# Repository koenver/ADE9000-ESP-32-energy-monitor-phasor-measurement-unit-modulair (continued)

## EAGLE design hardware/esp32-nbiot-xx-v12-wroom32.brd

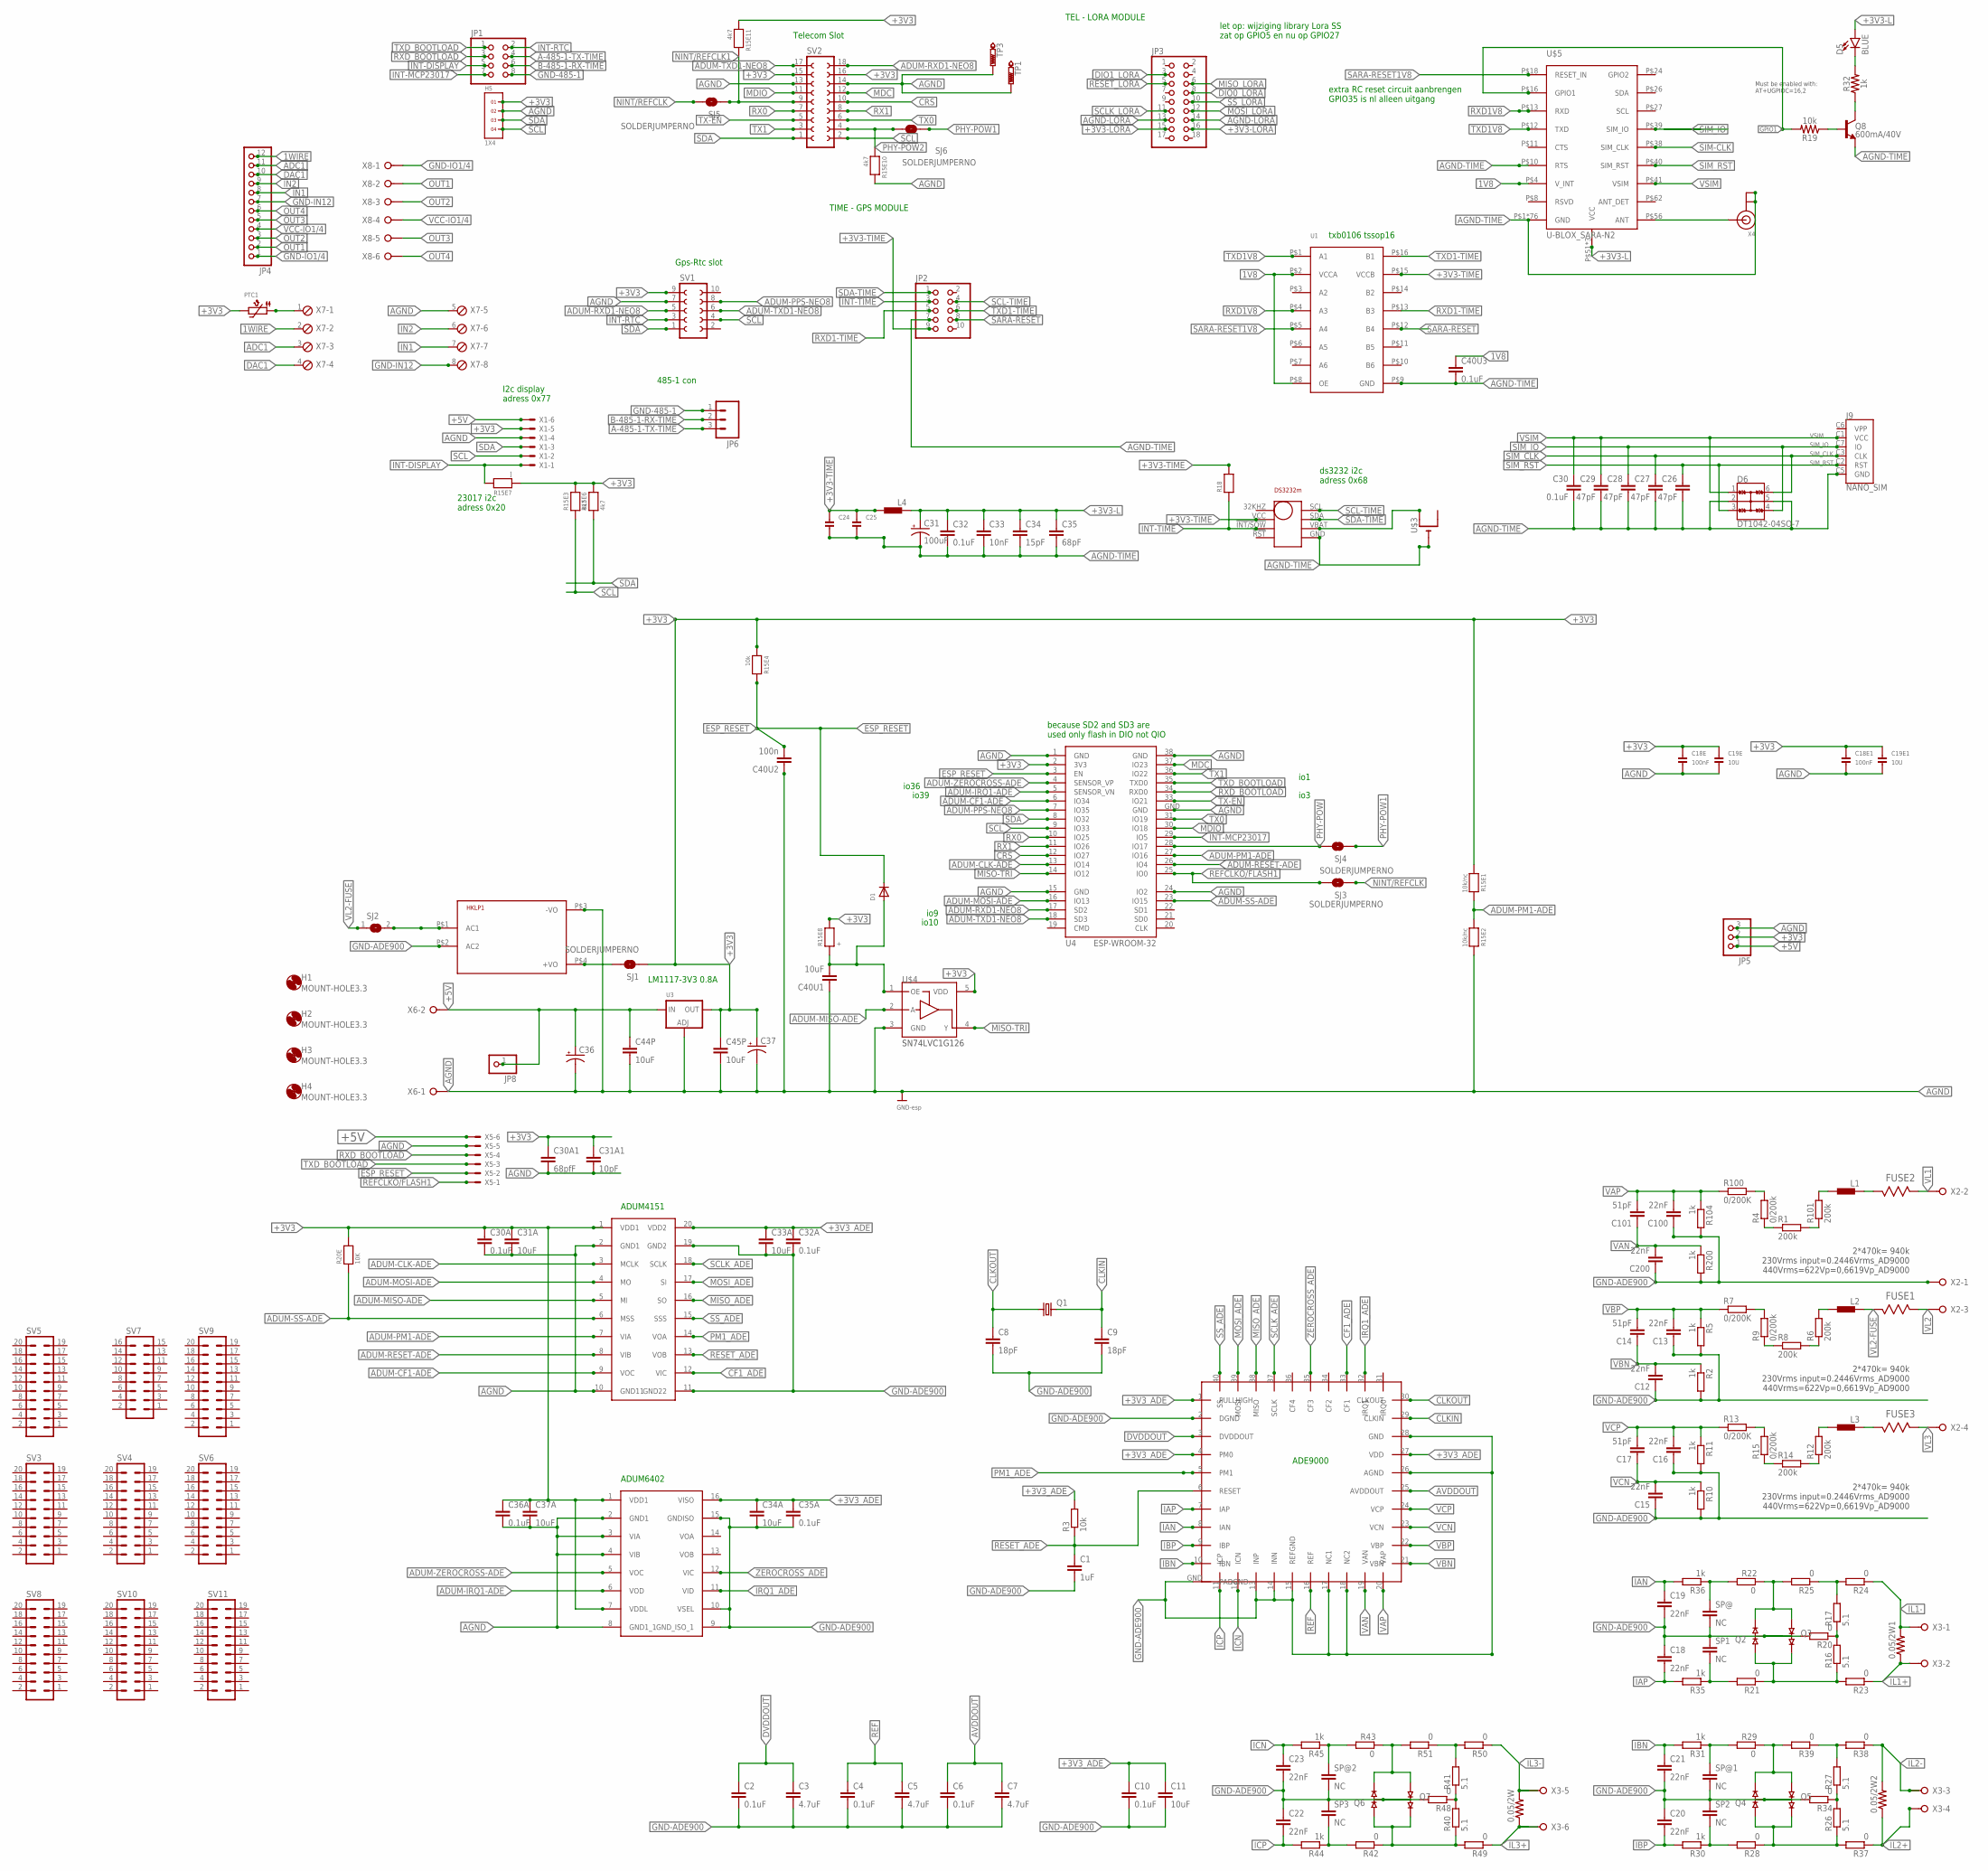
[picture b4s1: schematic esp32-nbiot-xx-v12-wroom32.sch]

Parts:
0.05/2W, 0.05/2W1, 0.05/2W2: R-US_R4527; R4527
ADE9000: ADE9000; LFCSP40
ADUM4151: ADUM4151; SOIC20R
ADUM6402-2: ADUM6402; SOIC16R
C1: 1uF; C0805
C2, C4, C6, C10, C30A, C32A, C35A, C36A, C40U3: 0.1uF; C0805
C3, C5, C7: 4.7uF; C0805
C8, C9: 18pF; C0805
C11, C31A, C33A, C34A, C37A, C40U1, C44P, C45P: 10uF; C0805
C12, C13, C15, C16, C18, C19, C20, C21, C22, C23, C100, C200: 22nF; C0805
C14, C17, C101: 51pF; C0805
C18E, C18E1: 100nF; _0805
C19E, C19E1: 10U; _0805
C24, C25: CAP_CERAMIC0805; 0805
C26, C27, C28, C29: 47pF; 0603
C30, C32: 0.1uF; 0603
C30A1: 68pfF; C0805
C31: 100uF; 1206-POLAR
C31A1: 10pF; C0805
C33: 10nF; 0603
C34: 15pF; 0603
C35: 68pF; 0603
C36, C37: CPOL-USD/7343-31R; D/7343-31R
C40U2: 100n; C0805
D1: DIODE_SOD-123FL; SOD-123FL
D5: BLUE; LED-0603
D6: DT1042-04SO-7; SOT23-6L
FUSE1, FUSE2, FUSE3: CRCW25124R70JNEG; RESC6332X71N
H1, H2, H3, H4: MOUNT-HOLE3.3; 3,3
H5: 1X4
HKLP1: HKLPM01
J9: NANO_SIM; NANO_SIM_WURTH_693043020611
JP1: PINHD-2X4; 2X04
JP2: PINHD-2X5/90; 2X05/90
JP3: PINHD-2X9/90; 2X09/90
JP4: PINHD-1X12; 1X12
JP5: PINHD-1X3; 1X03
JP6: M03SCREW; SCREWTERMINAL-3.5MM-3
JP8: PINHD-1X1; 1X01
L1, L2, L3, L4: 1500; M0805; DIGIKEY 490-1048-1-ND
PTC1: PTC1206; 1206
Q1: CRYSTALCTS406; CTS406
Q2, Q3, Q4, Q5, Q6, Q7: MMBD4148SE; SOT23-3; DIGIKEY MMBD4148SECT-ND
Q8: 600mA/40V; SOT23-3
R1, R6, R8, R12, R14, R101: 200k; M1206
R2, R5, R10, R11, R104, R200: 1k; M0805
R3: 10k; M0805
R4, R9, R15: 0/200k; M1206
R7, R13, R100: 0/200K; M1206
R15E1, R15E2: 10k/nc; _0805
R15E3, R15E6, R15E10, R15E11: 4k7; _0805
R15E4: 10k; _0805
R15E7: ]; _0805
R15E8: +; _0805
R16, R26, R40: 5.1; R0805; MFR_PART_NO_# CPF0805B5R1E1
R17, R27, R41: 5.1; R0805
R18: RESISTOR0805; 0805
R19: 10k; 0603
R20, R21, R22, R23, R24, R25, R28, R29, R34, R37, R38, R39, R42, R43, R48, R49, R50, R51: 0; R0603
R20E: 10K; _0805
R30, R31, R35, R36, R44, R45: 1k; R0603
R32: 1k; 0603
SJ1, SJ3, SJ4, SJ5, SJ6: SOLDERJUMPERNO; SJ_2S-NO
SJ2: SOLDERJUMPERWAVE; SOLDERJUMPER_WAVE
SP1, SP2, SP3: NC; C0805
SP@, SP@1, SP@2: NC; C0805
SV1: FE05-2W
SV2: FE09-2W
SV3, SV4, SV5, SV6, SV8, SV9, SV10, SV11: MA10-2
SV7: MA08-2
TP1, TP3: PTR1TP08SQ; TP08SQ
U1: TXB0106; TSSOP16
U3: LM1117SOT223-REFLOW; SOT223-R
U4: ESP-WROOM-32
U$1: DS3232M; SOIC8
U$3: CR1220SMT; CR1220-SMD
U$4: SN74LVC1G126DBVT; SOT-23-5L
U$5: U-BLOX_SARA-N2; SARA-N2
X1, X5: 22-23-2061
X2: W237-04P; W237-4P
X3, X8: W237-06P; W237-6P
X4: ANTENNA_U.FL; U.FL
X6: W237-02P; W237-132
X7: MPT8; 8POL254

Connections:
1V8: C40U3.1, U1.P$2 (VCCA), U1.P$8 (OE), U$5.P$4 (V_INT)
1WIRE: JP4.12, X7.2
+3V3: ADUM4151.1 (VDD1), ADUM6402-2.1 (VDD1), ADUM6402-2.7 (VDDL), C18E.1, C18E1.1, C19E.1, C19E1.1, C30A.1, C30A1.1, C31A.1, C31A1.1, C36A.1, C37.+, C37A.1, C45P.1, H5.1, JP5.2, PTC1.2, R15E1.1, R15E3.2, R15E4.1, R15E6.2, R15E7.1, R15E8.2, R15E11.1, R20E.2, SJ1.1, SV1.9, SV2.15, SV2.16, U3.2 (OUT), U4.2 (3V3), U$4.5 (VDD), X1.5
+3V3-L: C31.1 (+), C32.1, C33.1, C34.1, C35.1, D5.A, L4.1, U$5.P$51 (VCC), U$5.P$52 (VCC), U$5.P$53 (VCC)
+3V3-LORA: JP3.15, JP3.16
+3V3-TIME: C24.1, C25.1, JP2.9, L4.2, R18.2, U1.P$15 (VCCB), U$1.VCC
+3V3FUSE: PTC1.1, X7.1
+3V3_ADE: ADE9000.1 (PULLHIGH), ADE9000.4 (PM0), ADE9000.27 (VDD), ADUM4151.20 (VDD2), ADUM6402-2.16 (VISO), C10.1, C11.1, C32A.1, C33A.1, C34A.1, C35A.1, R3.2
+5V: C36.+, C44P.1, JP5.1, JP8.1, U3.3 (IN), X1.6, X5.6, X6.2
A-485-1-TX-TIME: JP1.4, JP6.3
ADC1: JP4.11, X7.3
ADUM-CF1-ADE: ADUM4151.9 (VOC), U4.6 (IO34)
ADUM-CLK-ADE: ADUM4151.3 (MCLK), U4.13 (IO14)
ADUM-IRQ1-ADE: ADUM6402-2.6 (VOD), U4.5 (SENSOR_VN)
ADUM-MISO-ADE: ADUM4151.5 (MI), U$4.2 (A)
ADUM-MOSI-ADE: ADUM4151.4 (MO), U4.16 (IO13)
ADUM-PM1-ADE: ADUM4151.7 (VIA), R15E1.2, R15E2.1, U4.27 (IO16)
ADUM-PPS-NEO8: SV1.8, U4.7 (IO35)
ADUM-RESET-ADE: ADUM4151.8 (VIB), U4.26 (IO4)
ADUM-RXD1-NEO8: SV1.5, SV2.18, U4.17 (SD2)
ADUM-SS-ADE: ADUM4151.6 (MSS), R20E.1, U4.23 (IO15)
ADUM-TXD1-NEO8: SV1.6, SV2.17, U4.18 (SD3)
ADUM-ZEROCROSS-ADE: ADUM6402-2.5 (VOC), U4.4 (SENSOR_VP)
AGND: ADUM4151.2 (GND1), ADUM4151.10 (GND11), ADUM6402-2.2 (GND1), ADUM6402-2.3 (VIA), ADUM6402-2.4 (VIB), ADUM6402-2.8 (GND1_1), C18E.2, C18E1.2, C19E.2, C19E1.2, C30A.2, C30A1.2, C31A.2, C31A1.2, C36.-, C36A.2, C37.-, C37A.2, C40U1.1, C40U2.1, C44P.2, C45P.2, H5.2, HKLP1.P$3 (-VO), JP5.3, R15E2.2, R15E10.2, SV1.7, SV2.13, SV2.14, TP1.TP, TP3.TP, U3.1 (ADJ), U4.1 (GND), U4.15 (GND), U4.24 (IO2), U4.38 (GND), U4.GND, U$4.3 (GND), X1.4, X5.5, X6.1, X7.5
AGND-LORA: JP3.13, JP3.14
AGND-TIME: C24.2, C25.2, C26.2, C27.2, C28.2, C29.2, C30.2, C31.2 (-), C32.2, C33.2, C34.2, C35.2, C40U3.2, D6.2, D6.5, J9.C5 (GND), JP2.7, Q8.2 (E), U1.P$9 (GND), U$1.GND, U$3.-, U$5.P$1 (GND), U$5.P$2 (GND), U$5.P$3 (GND), U$5.P$5 (GND), U$5.P$6 (GND), U$5.P$7 (GND), U$5.P$9 (GND), U$5.P$10 (RTS), U$5.P$14 (GND), U$5.P$15 (GND), U$5.P$17 (GND), U$5.P$19 (GND), U$5.P$20 (GND), U$5.P$21 (GND), U$5.P$22 (GND), U$5.P$23 (GND), U$5.P$25 (GND), U$5.P$28 (GND), U$5.P$29 (GND), U$5.P$30 (GND), U$5.P$31 (GND), U$5.P$32 (GND), U$5.P$33 (GND), U$5.P$34 (GND), U$5.P$35 (GND), U$5.P$36 (GND), U$5.P$37 (GND), U$5.P$42 (GND), U$5.P$43 (GND), U$5.P$44 (GND), U$5.P$45 (GND), U$5.P$46 (GND), U$5.P$47 (GND), U$5.P$48 (GND), U$5.P$49 (GND), U$5.P$50 (GND), U$5.P$54 (GND), U$5.P$55 (GND), U$5.P$57 (GND), U$5.P$58 (GND), U$5.P$59 (GND), U$5.P$60 (GND), U$5.P$61 (GND), U$5.P$63 (GND), U$5.P$64 (GND), U$5.P$65 (GND), U$5.P$66 (GND), U$5.P$67 (GND), U$5.P$68 (GND), U$5.P$69 (GND), U$5.P$70 (GND), U$5.P$71 (GND), U$5.P$72 (GND), U$5.P$73 (GND), U$5.P$74 (GND), U$5.P$75 (GND), U$5.P$76 (GND), U$5.P$77 (GND), U$5.P$78 (GND), U$5.P$79 (GND), U$5.P$80 (GND), U$5.P$81 (GND), U$5.P$82 (GND), U$5.P$83 (GND), U$5.P$84 (GND), U$5.P$85 (GND), U$5.P$86 (GND), U$5.P$87 (GND), U$5.P$88 (GND), U$5.P$89 (GND), U$5.P$90 (GND), U$5.P$91 (GND), U$5.P$92 (GND), U$5.P$93 (GND), U$5.P$94 (GND), U$5.P$95 (GND), U$5.P$96 (GND), X4.1 (GND), X4.2 (GND)
AVDDOUT: ADE9000.25 (AVDDOUT), C6.1, C7.1
B-485-1-RX-TIME: JP1.6, JP6.2
CF1_ADE: ADE9000.33 (CF1), ADUM4151.12 (VIC)
CLKIN: ADE9000.29 (CLKIN), C9.1, Q1.3 (2)
CLKOUT: ADE9000.30 (CLKOUT), C8.1, Q1.1
CRS: SV2.10, U4.12 (IO27)
DAC1: JP4.10, X7.4
DIO0_LORA: JP3.8
DIO1_LORA: JP3.3
DVDDOUT: ADE9000.3 (DVDDOUT), C2.1, C3.1
ESP_RESET: C40U2.2, D1.C, R15E4.2, U4.3 (EN), X5.2
GND-485-1: JP1.8, JP6.1
GND-ADE900: ADE9000.2 (DGND), ADE9000.13 (INP), ADE9000.14 (INN), ADE9000.15 (REFGND), ADE9000.17 (NC1), ADE9000.18 (NC2), ADE9000.26 (AGND), ADE9000.28 (GND), ADE9000.GND, ADUM4151.11 (GND22), ADUM4151.19 (GND2), ADUM6402-2.9 (GND_ISO_1), ADUM6402-2.10 (VSEL), ADUM6402-2.15 (GNDISO), C1.2, C2.2, C3.2, C4.2, C5.2, C6.2, C7.2, C8.2, C9.2, C10.2, C11.2, C12.1, C13.1, C15.1, C16.1, C18.1, C19.2, C20.1, C21.2, C22.1, C23.2, C32A.2, C33A.2, C34A.2, C35A.2, C100.1, C200.1, HKLP1.P$2 (AC2), Q2.3, Q3.3, Q4.3, Q5.3, Q6.3, Q7.3, R2.2, R5.2, R10.2, R11.2, R20.2, R34.2, R48.2, R104.2, R200.2, SP1.1, SP2.1, SP3.1, SP@.2, SP@1.2, SP@2.2, X2.1
GND-IN12: JP4.7, X7.8
GND-IO1/4: JP4.1, X8.1
GPIO1: R19.2, U$5.P$16 (GPIO1)
IAN: ADE9000.8 (IAN), C19.1, R36.2
IAP: ADE9000.7 (IAP), C18.2, R35.2
IBN: ADE9000.10 (IBN), C21.1, R31.2
IBP: ADE9000.9 (IBP), C20.2, R30.2
ICN: ADE9000.12 (ICN), C23.1, R45.2
ICP: ADE9000.11 (ICP), C22.2, R44.2
IL1+: 0.05/2W1.1, R23.1, X3.2
IL1-: 0.05/2W1.2, R24.1, X3.1
IL2+: 0.05/2W2.1, R37.1, X3.4
IL2-: 0.05/2W2.2, R38.1, X3.3
IL3+: 0.05/2W.1, R49.1, X3.6
IL3-: 0.05/2W.2, R50.1, X3.5
IN1: JP4.8, X7.7
IN2: JP4.9, X7.6
INT-DISPLAY: JP1.5, R15E7.2, X1.1
INT-MCP23017: JP1.7, U4.29 (IO5)
INT-RTC: JP1.2, SV1.3
INT-TIME: JP2.3, R18.1, U$1.!INT/!!SQW
IRQ1_ADE: ADE9000.32 (IRQ1), ADUM6402-2.11 (VID)
MDC: SV2.12, U4.37 (IO23)
MDIO: SV2.11, U4.30 (IO18)
MISO-TRI: U4.14 (IO12), U$4.4 (Y)
MISO_ADE: ADE9000.38 (MISO), ADUM4151.16 (SO)
MISO_LORA: JP3.6
MOSI_ADE: ADE9000.39 (MOSI), ADUM4151.17 (SI)
MOSI_LORA: JP3.12
unnamed: L2.2, R6.2
unnamed: Q2.1, Q3.2, R16.1, R21.1, R23.2
unnamed: R7.2, R9.2
unnamed: R8.1, R9.1
unnamed: C40U1.2, D1.A, R15E8.1, U$4.1 (OE)
unnamed: U$1.VBAT, U$3.+$1 (+)
unnamed: R6.1, R8.2
unnamed: Q2.2, Q3.1, R22.2, R25.2
unnamed: L3.2, R12.2
unnamed: FUSE3.1, L3.1
unnamed: R13.2, R15.2
unnamed: R14.1, R15.1
unnamed: R12.1, R14.2
unnamed: R22.1, R36.1, SP@.1
unnamed: Q8.1 (B), R19.1
unnamed: R16.2, R17.1, R20.1
unnamed: HKLP1.P$1 (AC1), SJ2.2
unnamed: R17.2, R24.2, R25.1
unnamed: Q4.1, Q5.2, R26.1, R28.1, R37.2
unnamed: D5.C, R32.2
unnamed: Q4.2, Q5.1, R29.2, R39.2
unnamed: R29.1, R31.1, SP@1.1
unnamed: Q8.3 (C), R32.1
unnamed: U$5.P$56 (ANT), X4.3 (SIGNAL)
unnamed: R28.2, R30.1, SP2.2
unnamed: R4.2, R100.2
unnamed: R26.2, R27.1, R34.1
unnamed: L1.2, R101.2
unnamed: R27.2, R38.2, R39.1
unnamed: R1.1, R4.1
unnamed: R1.2, R101.1
unnamed: R21.2, R35.1, SP1.2
unnamed: Q6.1, Q7.2, R40.1, R42.1, R49.2
unnamed: Q6.2, Q7.1, R43.2, R51.2
unnamed: R43.1, R45.1, SP@2.1
unnamed: R42.2, R44.1, SP3.2
unnamed: R40.2, R41.1, R48.1
unnamed: R41.2, R50.2, R51.1
unnamed: HKLP1.P$4 (+VO), SJ1.2
NINT/REFCLK: SJ3.1, SJ5.2
NINT/REFCLK1: R15E11.2, SJ5.1, SV2.9
OUT1: JP4.2, X8.2
OUT2: JP4.3, X8.3
OUT3: JP4.5, X8.5
OUT4: JP4.6, X8.6
PHY-POW: SJ4.2, U4.28 (IO17)
PHY-POW1: SJ4.1, SJ6.1
PHY-POW2: R15E10.1, SJ6.2, SV2.4
PM1_ADE: ADE9000.5 (PM1), ADUM4151.14 (VOA)
REF: ADE9000.16 (REF), C4.1, C5.1
REFCLKO/FLASH1: SJ3.2, U4.25 (IO0), X5.1
RESET_ADE: ADE9000.6 (RESET), ADUM4151.13 (VOB), C1.1, R3.1
RESET_LORA: JP3.5
RX0: SV2.7, U4.10 (IO25)
RX1: SV2.8, U4.11 (IO26)
RXD1-TIME: JP2.5, U1.P$13 (B3)
RXD1V8: U1.P$4 (A3), U$5.P$13 (RXD)
RXD_BOOTLOAD: JP1.3, U4.34 (RXD0), X5.4
SARA-RESET: JP2.8, U1.P$12 (B4)
SARA-RESET1V8: U1.P$5 (A4), U$5.P$18 (RESET_IN)
SCL: H5.4, R15E3.1, SV1.4, SV2.2, U4.9 (IO33), X1.2
SCL-TIME: JP2.4, U$1.SCL
SCLK_ADE: ADE9000.37 (SCLK), ADUM4151.18 (SCLK)
SCLK_LORA: JP3.11
SDA: H5.3, R15E6.1, SV1.1, SV2.1, U4.8 (IO32), X1.3
SDA-TIME: JP2.1, U$1.SDA
SIM-CLK: U$5.P$38 (SIM_CLK)
SIM_CLK: C27.1, D6.6, J9.C3 (CLK)
SIM_IO: C28.1, D6.4, J9.C7 (IO), U$5.P$39 (SIM_IO)
SIM_RST: C26.1, D6.3, J9.C2 (RST), U$5.P$40 (SIM_RST)
SS_ADE: ADE9000.40 (SS), ADUM4151.15 (SSS)
SS_LORA: JP3.10
TX0: SV2.6, U4.31 (IO19)
TX1: SV2.3, U4.36 (IO22)
TX-EN: SV2.5, U4.33 (IO21)
TXD1-TIME: JP2.6, U1.P$16 (B1)
TXD1V8: U1.P$1 (A1), U$5.P$12 (TXD)
TXD_BOOTLOAD: JP1.1, U4.35 (TXD0), X5.3
VAN: ADE9000.19 (VAN), C101.1, C200.2, R200.1
VAP: ADE9000.20 (VAP), C100.2, C101.2, R100.1, R104.1
VBN: ADE9000.21 (VBN), C12.2, C14.1, R2.1
VBP: ADE9000.22 (VBP), C13.2, C14.2, R5.1, R7.1
VCC-IO1/4: JP4.4, X8.4
VCN: ADE9000.23 (VCN), C15.2, C17.1, R10.1
VCP: ADE9000.24 (VCP), C16.2, C17.2, R11.1, R13.1
VL1: FUSE2.2, X2.2
VL1-FUSE: FUSE2.1, L1.1
VL2: FUSE1.2, X2.3
VL2-FUSE: FUSE1.1, L2.1, SJ2.1
VL3: FUSE3.2, X2.4
VSIM: C29.1, C30.1, D6.1, J9.C1 (VCC), U$5.P$41 (VSIM)
ZEROCROSS_ADE: ADE9000.35 (CF3), ADUM6402-2.12 (VIC)

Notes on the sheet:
ADUM4151
2*470k= 940k 230Vrms input=0.2446Vrms_AD9000 440Vrms=622Vp=0,6619Vp_AD9000
ADE9000
ADUM6402
LM1117-3V3 0.8A
23017 i2c adress 0x20
I2c display adress 0x77
Telecom Slot
Gps-Rtc slot
let op: wijziging library Lora SS zat op GPIO5 en nu op GPIO27
TEL - LORA MODULE
TIME - GPS MODULE
485-1 con
io36
io39
io1
io3
because SD2 and SD3 are used only flash in DIO not QIO
io9
io10
ds3232 i2c adress 0x68
Must be enabled with: AT+UGPIOC=16,2
txb0106 tssop16
extra RC reset circuit aanbrengen GPIO35 is nl alleen uitgang

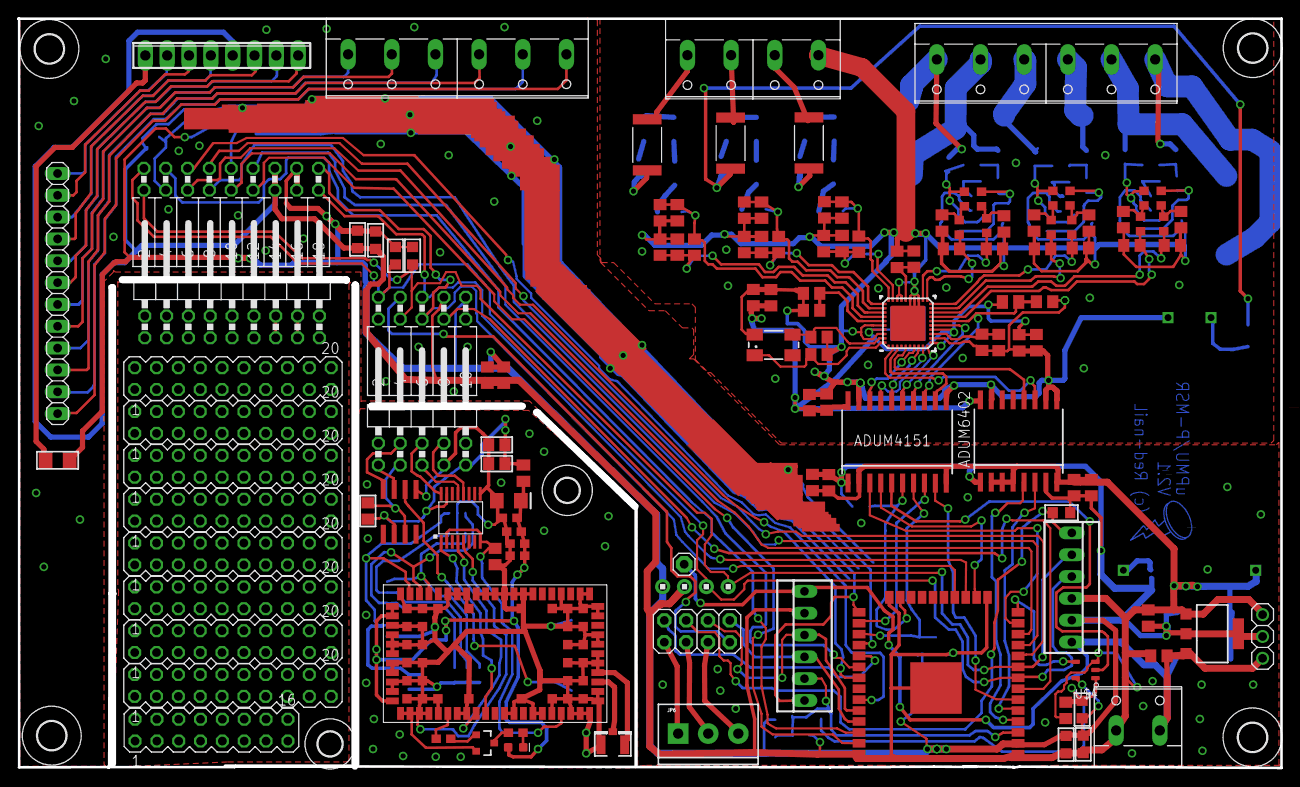
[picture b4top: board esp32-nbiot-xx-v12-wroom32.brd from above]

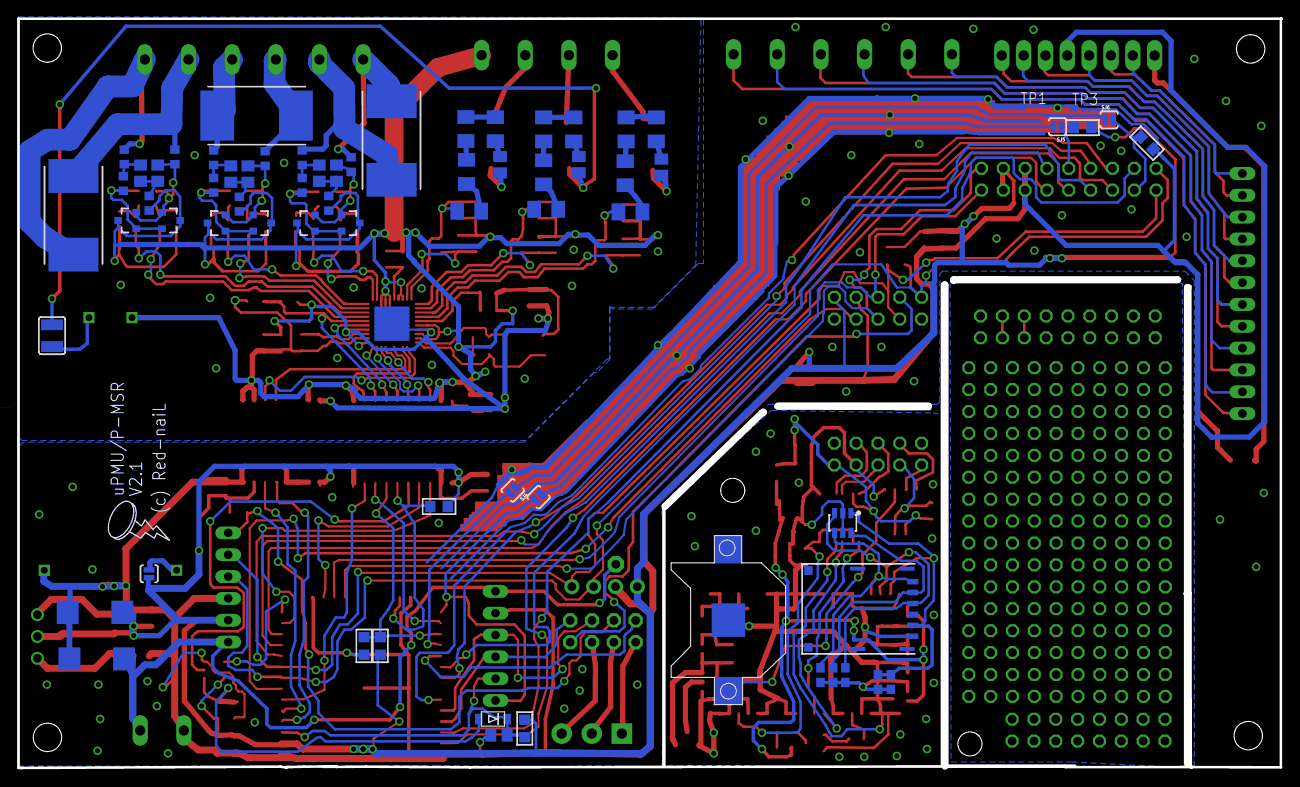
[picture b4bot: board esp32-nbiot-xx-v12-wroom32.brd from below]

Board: 2 copper layers, 146.9 x 87.2 mm, 202 parts (68 on the bottom side), 152 nets.

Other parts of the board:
U$7, U$8: 2,8

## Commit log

2020-05-22 Create Hardware
2020-05-22 Create eagle
2020-05-22 Create photo
2020-05-22 Create file
2020-05-22 Create 485 interface test
2020-05-22 Create file
2020-05-22 Create files
2020-05-24 Create test status hardware
2020-05-24 Create programmer
2020-05-26 Update test status hardware
